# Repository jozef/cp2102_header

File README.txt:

USB to TTL header using cp2102 chip that has nearly the size of
PinSocket_1x06_P2.54mm_Horizontal header. So that either PinSocket can be
soldered or when permanent micro USB is needed this board.

For pictures and more description see:
https://blog.kutej.net/2019/07/cp2102-ttl2usb-header

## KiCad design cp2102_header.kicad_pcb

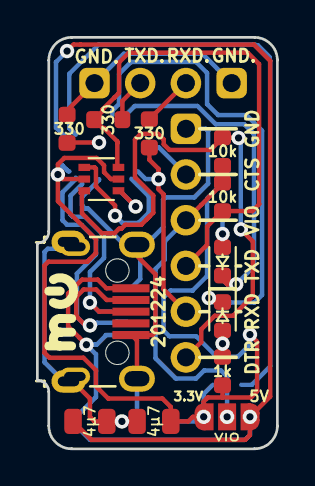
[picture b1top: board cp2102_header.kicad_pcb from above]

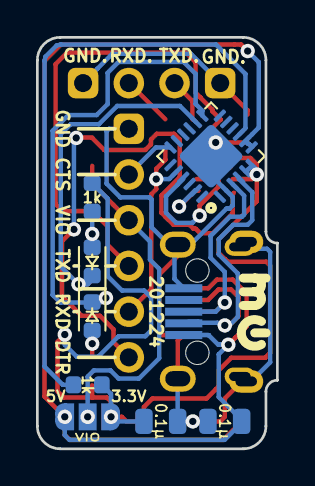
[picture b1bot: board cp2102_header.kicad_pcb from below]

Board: 2 copper layers, 13.3 x 22.9 mm, 23 parts (8 on the bottom side), 20 nets.

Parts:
C21, C23: 4μ7; C_0805_2012Metric_no_lines
C22, C24: 0.1μ; C_0805_2012Metric_no_lines
D21, D23: TX_LED; LED_0603_1608Metric_symbol
D22, D24: RX_LED; LED_0603_1608Metric_symbol
J1: FTDI; PinSocket_1x06_P2.54mm_Vertical_no_lines
J2: USB_B_Micro; USB_Micro-B_Wuerth_629105150521_plus_Pitch_7.2mm_doubleside
J8: Serial; PinHeader_1x04_P2.54mm_Vertical_no_lines
JP9, JP9#2: SJMP; SolderJumper-3_P1.3mm_Open_RoundedPad1.0x1.5mm_no_arrow_no_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
Q3: BSS138PS; SOT-363_SC-70-6_dot
R2, R21, R22: 1k; R_0603_1608Metric_no_lines
R33, R36: 10k; R_0603_1608Metric_no_lines
R37, R47, R57: 330; R_0603_1608Metric_no_lines
U2: CP2102N; QFN-24-1EP_4x4mm_P0.5mm_EP2.6x2.6mm

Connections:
+3V3: C21.1, C22.1, JP9.3, JP9#2.3, Q3.2, Q3.5, R2.2, R21.2, R22.2, U2.5, U2.6
+5V: C23.1, C24.1, J2.1, JP9.1, JP9#2.1, U2.7, U2.8
CTS: J1.2, U2.18
D+: J2.3, U2.3
D-: J2.2, U2.4
DTR: J1.6, Q3.3, R33.1
GND: C21.2, C22.2, C23.2, C24.2, J1.1, J2.5, J2.6, R57.2, U2.2, U2.25
GNDr: J8.1, J8.4, R57.1
unnamed: D21.2, D23.2, R21.1
unnamed: D22.2, D24.2, R22.1
unnamed: R2.1, U2.9
RXD: J1.5, R47.2, U2.20
RXDr: J8.3, R47.1
RXL: D22.1, D24.1, U2.13
TXD: J1.4, Q3.6, R36.1, R37.2
TXDr: J8.2, R37.1
TXL: D21.1, D23.1, U2.14
U_DTR: Q3.4, U2.23
U_TXD: Q3.1, U2.21
VIO: J1.3, JP9.2, JP9#2.2, R33.2, R36.2

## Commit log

2019-07-30 initial version
2019-08-05 solder jumper instead of two resistors
2019-08-05 usb connector can be soldered on both sides
2019-09-10 add one extra pin for fixation, bigger labels, more/cleaner F/B-Silk lines
2019-09-20 move R around, full link on F.SilkS, bigger 2 gnd copper pads on usb from connector
2019-09-22 tx/rx leds on both sides
2019-09-22 round mounting hole, add more SilkS lines
2019-09-23 tracks clean-up
2019-09-29 switch to 0.5A trip current fuse
2019-10-06 move extra gnd pin
2019-11-02 allow for second type of micro usb connector
2019-11-02 replace tantalum with ceramic capacitors
2019-11-06 compact dimensions
2019-11-23 even smaller pcb, only one R per pair of tx/rx leds
2019-11-24 use less parts, cp2102 uart inputs are 5V tollerant
2019-12-06 more space for cp2102n, move capacitor away from header pin
2019-12-11 more resistor away from pin
2020-01-06 remove 2x pull-up R on tx-only side, tidy-up
2020-01-06 compacter placement
2020-01-08 rm unused labels
2020-01-15 add extra tx,rx (now with current protection resistors) and gnd on side, remove fuse
2020-01-15 fix labels orientation
2020-01-19 resistors as current protection only on extra tx/rx pins
2020-01-22 add resistors also to extra gnd pins
2020-01-25 tidy-up
2020-01-31 move around / tidy-up labels
2020-05-31 add D so that 5V is never feeded back to usb
2020-12-23 Revert "add D so that 5V is never feeded back to usb"
    This reverts commit 1b7cb2785b55f00b85a020102ccc41a40065f86b.
2020-12-23 revert back to previous version
